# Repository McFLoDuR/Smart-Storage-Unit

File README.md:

# Smart-Storage-Unit
Diploma Thesis of Fabian Reiner, Stefan Zauper and Rudolf Migirov

Nothin' much to see here.
Just uploaded our diploma thesis to github after completing it. (Created it to use during development (as intended) but forgot and soooo... yeah.)

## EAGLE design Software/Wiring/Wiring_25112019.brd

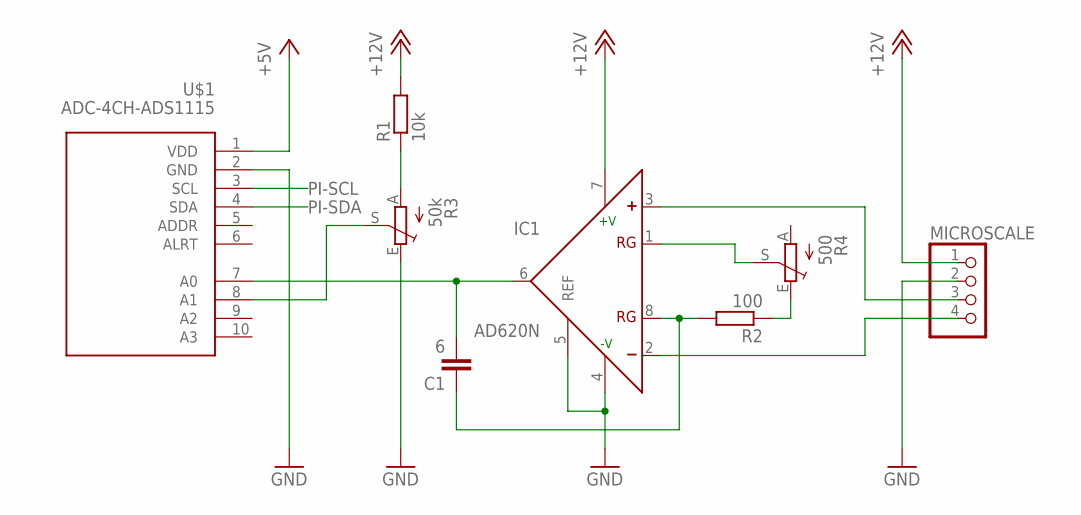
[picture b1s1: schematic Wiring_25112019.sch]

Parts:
C1: 6; C025-024X044
IC1: AD620N; DIL08
MICROSCALE: PINHD-1X4; 1X04
R1: 10k; 0204/5
R2: 100; 0204/5
R3: 50k; LI10
R4: 500; LI10
U$1: ADC-4CH-ADS1115

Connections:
+5V: U$1.1 (VDD)
+12V: IC1.7 (+V), MICROSCALE.1, R1.2
GND: IC1.4 (-V), IC1.5 (REF), MICROSCALE.2, R3.E, U$1.2 (GND)
unnamed: C1.2, IC1.6 (OUT), U$1.7 (A0)
unnamed: C1.1, IC1.8 (RG), R2.2
unnamed: IC1.1 (RG), R4.S
unnamed: R2.1, R4.E
unnamed: IC1.2 (-), MICROSCALE.4
unnamed: IC1.3 (+), MICROSCALE.3
unnamed: R1.1, R3.A
unnamed: R3.S, U$1.8 (A1)
PI-SCL: U$1.3 (SCL)
PI-SDA: U$1.4 (SDA)

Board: 2 copper layers, 8 parts (0 on the bottom side), 10 nets, no tracks yet.

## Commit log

2020-08-29 Uhmm.. Forgot the repo existed. There you have it - the finished product - THE SMART STORAGE UNIT DIPLOMA THESIS.
2020-08-29 Created README

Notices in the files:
parts and their libraries:
diy-modules: Released under the Creative Commons Attribution 4.0 International License: http://creativecommons.org/licenses/by/4.0
